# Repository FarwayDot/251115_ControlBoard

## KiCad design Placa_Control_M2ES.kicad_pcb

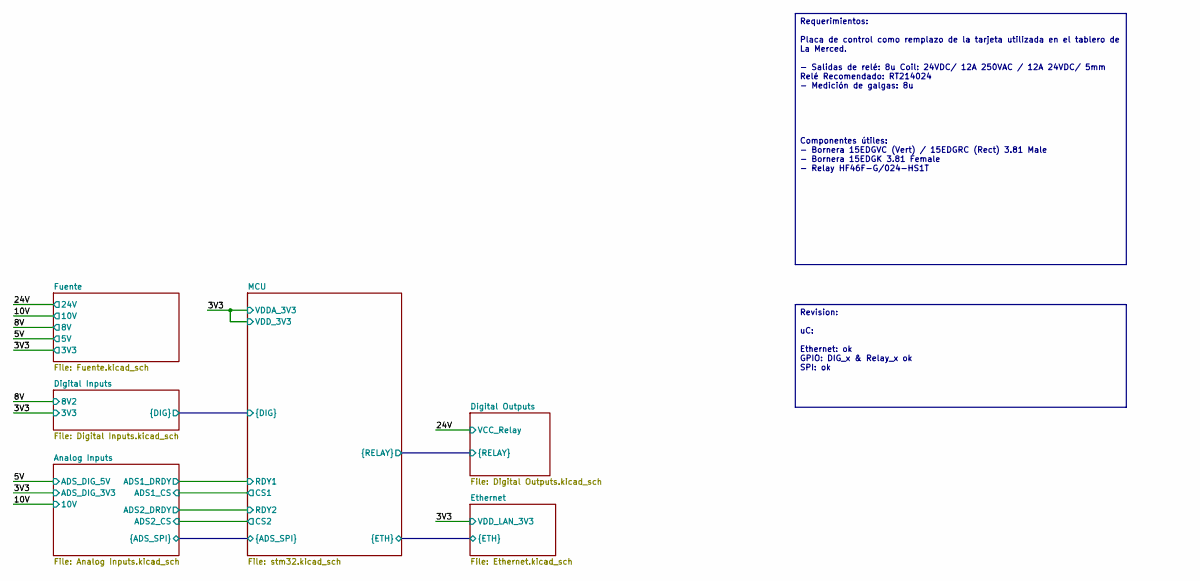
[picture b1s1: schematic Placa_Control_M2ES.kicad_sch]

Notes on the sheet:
Requerimientos: Placa de control como remplazo de la tarjeta utilizada en el tablero de La Merced. - Salidas de relé: 8u Coil: 24VDC/ 12A 250VAC / 12A 24VDC/ 5mm Relé Recomendado: RT214024 - Medición de galgas: 8u Componentes útiles: - Bornera 15EDGVC (Vert) / 15EDGRC (Rect) 3.81 Male - Bornera 15E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
Revision: uC: Ethernet: ok GPIO: DIG_x & Relay_x ok SPI: ok

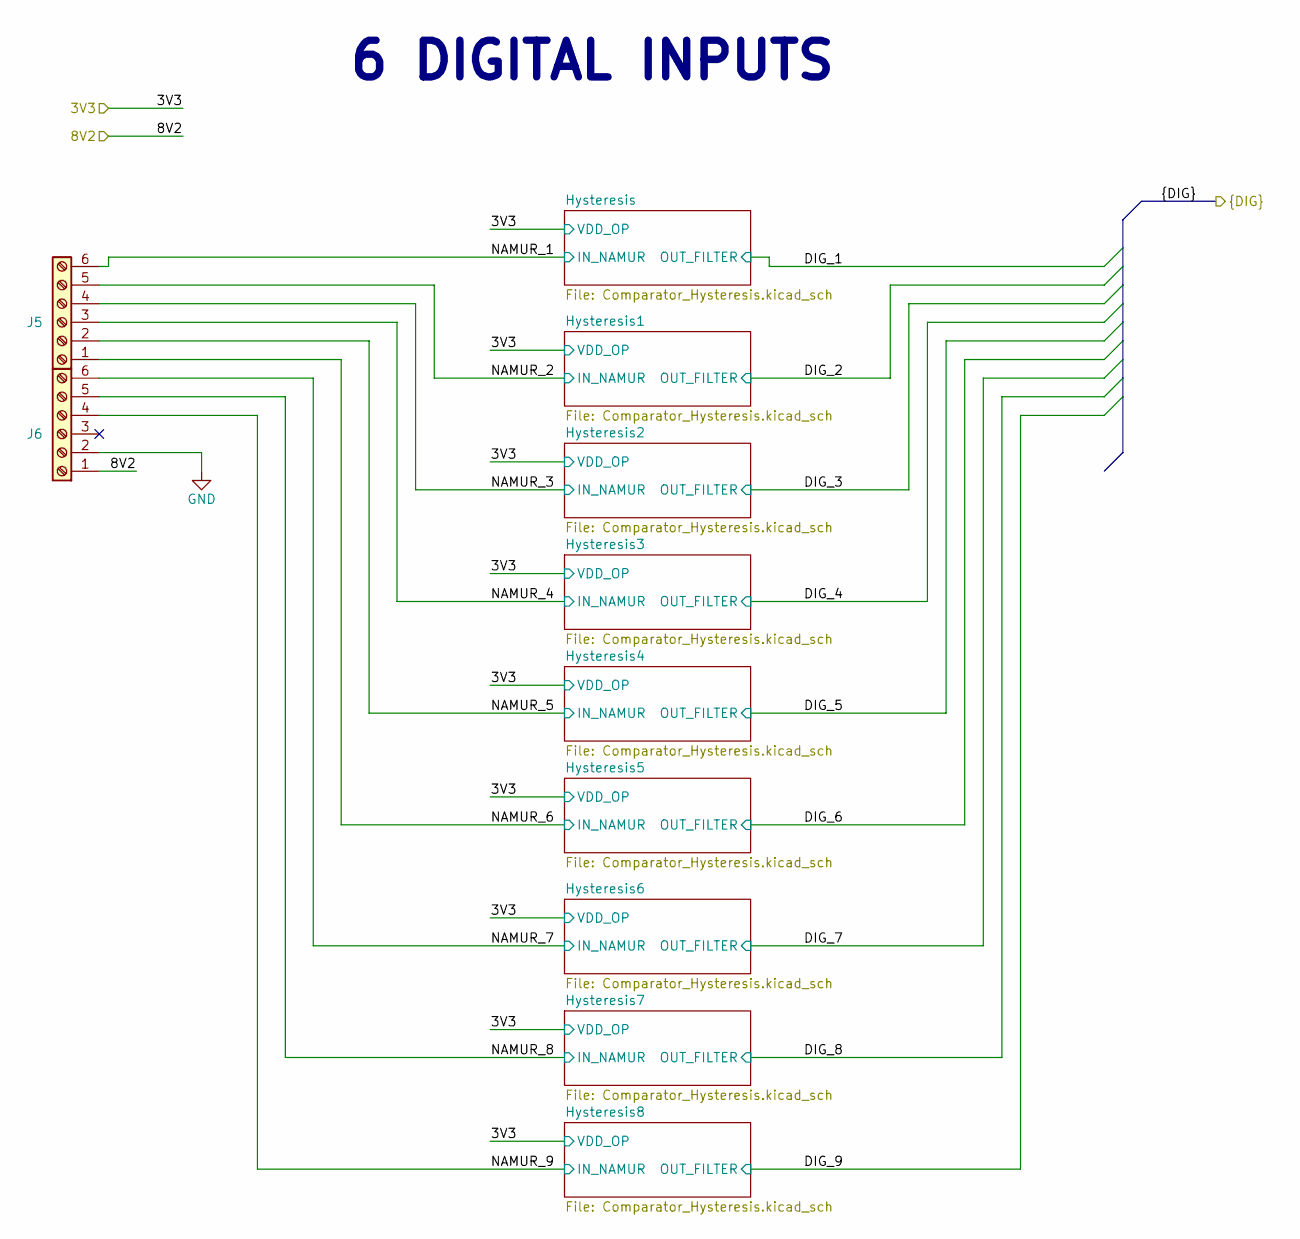
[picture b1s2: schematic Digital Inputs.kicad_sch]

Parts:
J5, J6: Screw_Terminal_01x06; 15EDGVC_6P_3.81mm_Male-Vert_Degson

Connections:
/8V: J6.1; also elsewhere on the board
/Digital Inputs/NAMUR_1: J5.6; also elsewhere on the board
/Digital Inputs/NAMUR_2: J5.5; also elsewhere on the board
/Digital Inputs/NAMUR_3: J5.4; also elsewhere on the board
/Digital Inputs/NAMUR_4: J5.3; also elsewhere on the board
/Digital Inputs/NAMUR_5: J5.2; also elsewhere on the board
/Digital Inputs/NAMUR_6: J5.1; also elsewhere on the board
/Digital Inputs/NAMUR_7: J6.6; also elsewhere on the board
/Digital Inputs/NAMUR_8: J6.5; also elsewhere on the board
/Digital Inputs/NAMUR_9: J6.4; also elsewhere on the board
GND: J6.2; also elsewhere on the board

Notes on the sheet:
6 DIGITAL INPUTS

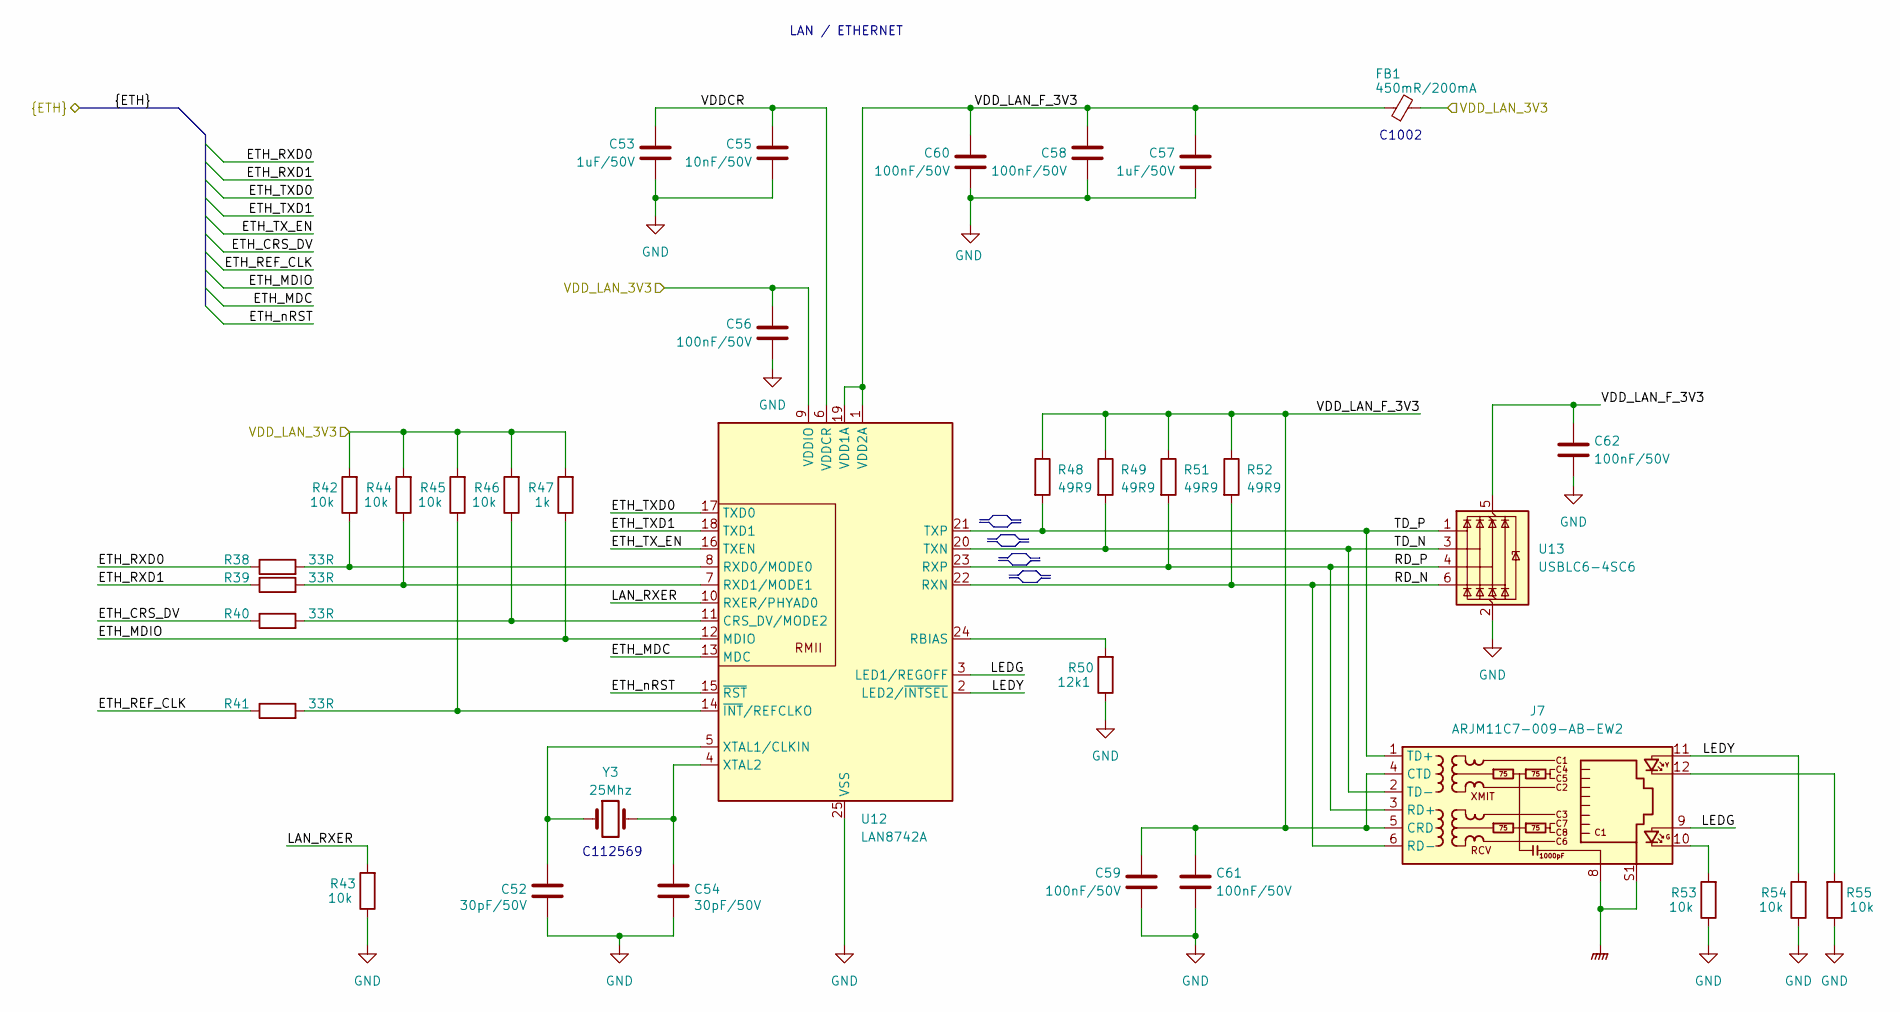
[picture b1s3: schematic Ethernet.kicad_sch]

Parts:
C52, C54: 30pF/50V; C_0603_1608Metric
C53, C57: 1uF/50V; C_0805_2012Metric
C55: 10nF/50V; C_0603_1608Metric
C56, C58, C59, C60, C61, C62: 100nF/50V; C_0603_1608Metric
FB1: 450mR/200mA; L_0603_1608Metric
J7: ARJM11C7-009-AB-EW2; ARJM11C7-009-AB-EW2_Abracon
R38, R39, R40, R41: 33R; R_0603_1608Metric
R42, R43, R44, R45, R46, R53, R54, R55: 10k; R_0603_1608Metric
R47: 1k; R_0603_1608Metric
R48, R49, R51, R52: 49R9; R_0603_1608Metric
R50: 12k1; R_0603_1608Metric
U12: LAN8742A; VQFN-24-1EP_4x4mm_P0.5mm_EP2.5x2.5mm_ThermalVias
U13: USBLC6-4SC6; SOT-23-6
Y3: 25Mhz; Crystal_SMD_5032-2Pin_5.0x3.2mm

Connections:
/Ethernet/ETH_CRS_DV: R40.1; also elsewhere on the board
/Ethernet/ETH_MDC: U12.13 (MDC); also elsewhere on the board
/Ethernet/ETH_MDIO: R47.1, U12.12 (MDIO); also elsewhere on the board
/Ethernet/ETH_REF_CLK: R41.1; also elsewhere on the board
/Ethernet/ETH_RXD0: R38.1; also elsewhere on the board
/Ethernet/ETH_RXD1: R39.1; also elsewhere on the board
/Ethernet/ETH_TXD0: U12.17 (TXD0); also elsewhere on the board
/Ethernet/ETH_TXD1: U12.18 (TXD1); also elsewhere on the board
/Ethernet/ETH_TX_EN: U12.16 (TXEN); also elsewhere on the board
/Ethernet/ETH_nRST: U12.15 (~RST); also elsewhere on the board
/Ethernet/LAN_RXER: R43.2, U12.10 (RXER/PHYAD0)
/Ethernet/LEDG: J7.9, U12.3 (LED1/REGOFF)
/Ethernet/LEDY: J7.11, R54.2, U12.2 (LED2/~INTSEL)
/Ethernet/RD_N: J7.6 (RD-), R52.2, U12.22 (RXN), U13.6 (I/O4)
/Ethernet/RD_P: J7.3 (RD+), R51.2, U12.23 (RXP), U13.4 (I/O3)
/Ethernet/TD_N: J7.2 (TD-), R49.2, U12.20 (TXN), U13.3 (I/O2)
/Ethernet/TD_P: J7.1 (TD+), R48.2, U12.21 (TXP), U13.1 (I/O1)
/Ethernet/VDDCR: C53.1, C55.1, U12.6 (VDDCR)
/Ethernet/VDD_LAN_F_3V3: C57.1, C58.1, C59.1, C60.1, C61.1, C62.1, FB1.1, J7.4 (CTD), J7.5 (CRD), R48.1, R49.1, R51.1, R52.1, U12.1 (VDD2A), U12.19 (VDD1A), U13.5 (VBUS)
GND: C52.2, C53.2, C54.2, C55.2, C56.2, C57.2, C58.2, C59.2, C60.2, C61.2, C62.2, R43.1, R50.1, R53.1, R54.1, R55.1, U12.25 (VSS), U13.2 (GND); also elsewhere on the board
GNDPWR: J7.8, J7.S1, J7.S2
unnamed: J7.10, R53.2
unnamed: J7.12, R55.2
unnamed: R40.2, R46.1, U12.11 (CRS_DV/MODE2)
unnamed: R50.2, U12.24 (RBIAS)
unnamed: R38.2, R42.1, U12.8 (RXD0/MODE0)
unnamed: R39.2, R44.1, U12.7 (RXD1/MODE1)
unnamed: C52.1, U12.5 (XTAL1/CLKIN), Y3.1
unnamed: C54.1, U12.4 (XTAL2), Y3.2
unnamed: R41.2, R45.1, U12.14 (~INT/REFCLKO)

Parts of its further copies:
R14, R17, R19, R21, R23, R24, R25: 10k; R_0603_1608Metric

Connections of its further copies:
/Analog Inputs/IN1_N: R23.2, R25.1; also elsewhere on the board
/Analog Inputs/IN2_N: R17.1; also elsewhere on the board
/Analog Inputs/IN2_P: R14.1; also elsewhere on the board
/Analog Inputs/IN3_N: R19.2, R21.1; also elsewhere on the board
/Analog Inputs/SENS1_A: R24.2; also elsewhere on the board
/Analog Inputs/SENS1_B: R25.2; also elsewhere on the board
/Analog Inputs/SENS2_B: R17.2; also elsewhere on the board
/Analog Inputs/SENS3_B: R21.2; also elsewhere on the board
GND: R14.2, R19.1, R23.1; also elsewhere on the board

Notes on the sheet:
C112569
C1002
LAN / ETHERNET

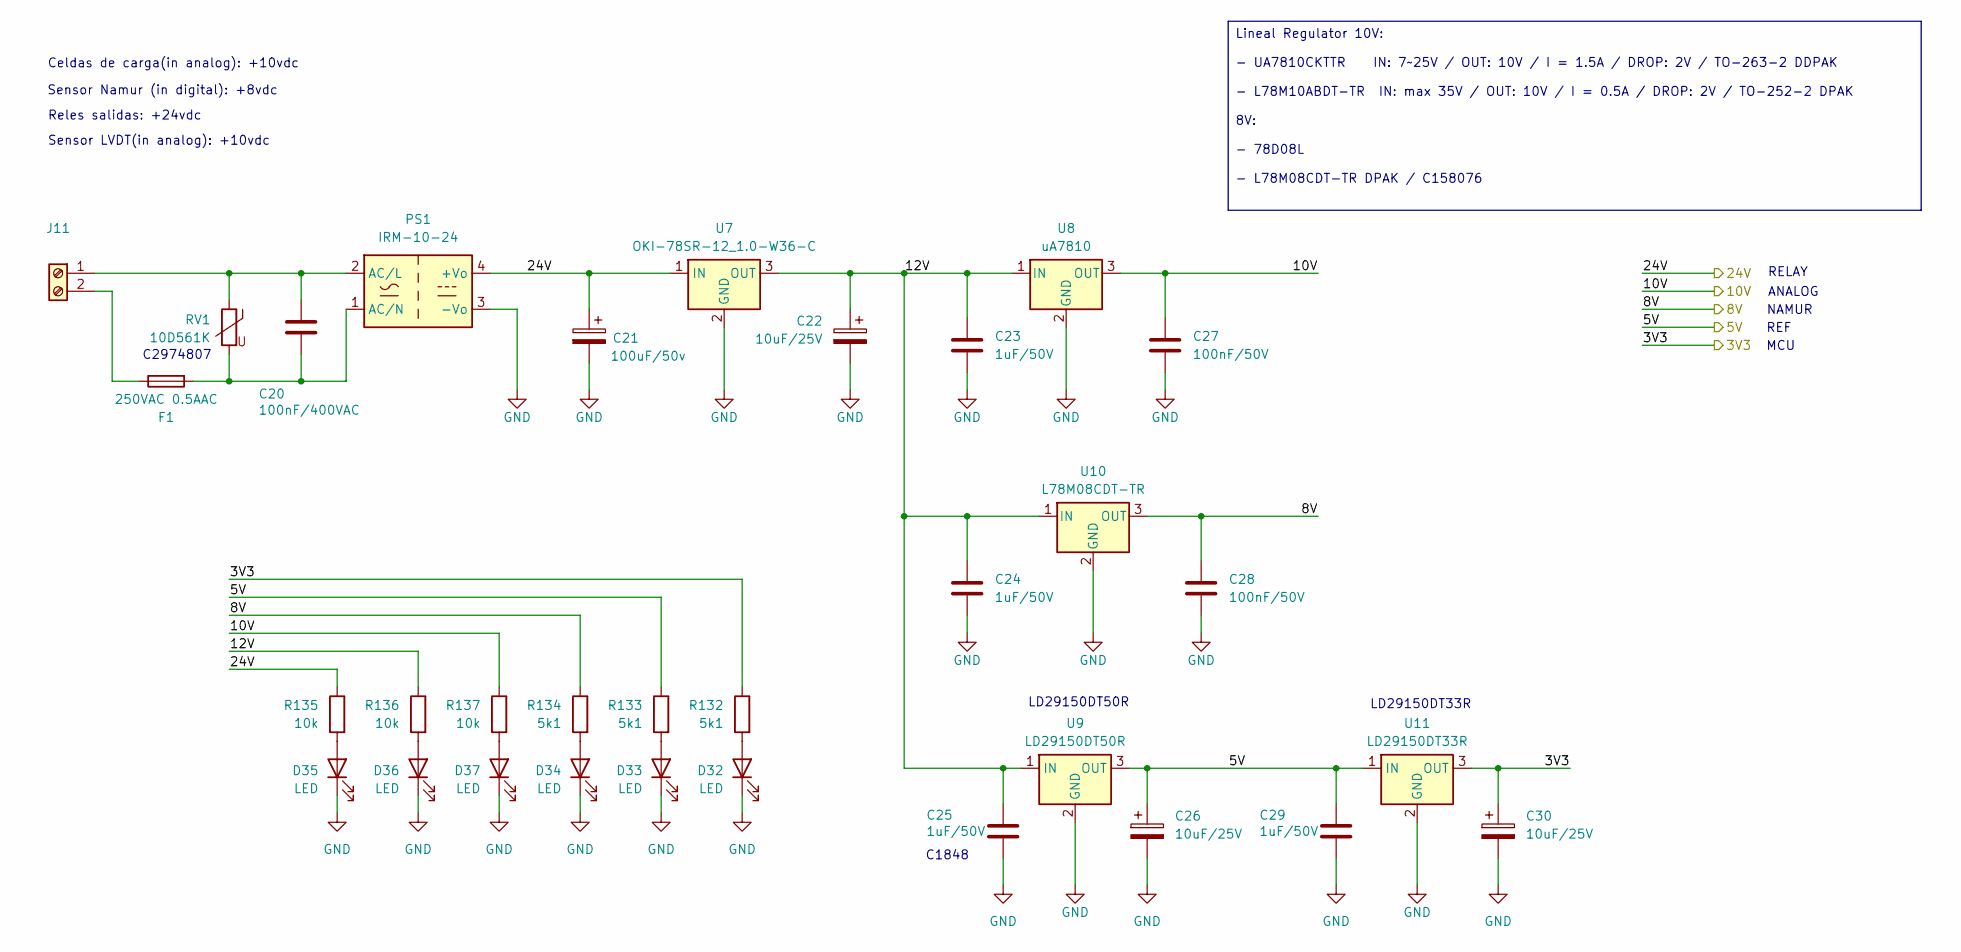
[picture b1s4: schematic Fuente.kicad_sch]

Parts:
C20: 100nF/400VAC; C_Disc_D10.5mm_W5.0mm_P7.50mm
C21: 100uF/50v; CP_Radial_D10.0mm_P5.00mm
C22, C26, C30: 10uF/25V; CP_Radial_D5.0mm_P2.50mm
C23, C24, C25, C29: 1uF/50V; C_1206_3216Metric
C27, C28: 100nF/50V; C_0603_1608Metric
D32, D33, D34, D35, D36, D37: LED; LED_0805_2012Metric
F1: 250VAC 0.5AAC; Fuseholder_TR5_Littelfuse_No560_No460
J11: Screw_Terminal_01x02; DG126_5.0_02P
PS1: IRM-10-24; Converter_ACDC_MeanWell_IRM-10-xx_THT
R132, R133, R134: 5k1; R_0603_1608Metric
R135, R136, R137: 10k; R_0603_1608Metric
RV1: 10D561K; RV_Disc_D12mm_W3.9mm_P7.5mm
U7: OKI-78SR-12_1.0-W36-C; Converter_DCDC_Murata_OKI-78SR_Vertical
U8: uA7810; TO-263-3_TabPin2
U9: LD29150DT50R; TO-252-2
U10: L78M08CDT-TR; TO-252-2
U11: LD29150DT33R; TO-252-2

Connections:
/5V: C26.1, C29.1, R133.1, U9.3 (OUT), U11.1 (IN); also elsewhere on the board
/8V: C28.1, R134.1, U10.3 (OUT); also elsewhere on the board
/10V: C27.1, R137.1, U8.3 (OUT); also elsewhere on the board
/24V: C21.1, PS1.4 (+Vo), R135.1, U7.1 (IN); also elsewhere on the board
/Fuente/12V: C22.1, C23.1, C24.1, C25.1, R136.1, U7.3 (OUT), U8.1 (IN), U9.1 (IN), U10.1 (IN)
GND: C21.2, C22.2, C23.2, C24.2, C25.2, C26.2, C27.2, C28.2, C29.2, C30.2, D32.1 (K), D33.1 (K), D34.1 (K), D35.1 (K), D36.1 (K), D37.1 (K), PS1.3 (-Vo), U7.2 (GND), U8.2 (GND), U9.2 (GND), U10.2 (GND), U11.2 (GND); also elsewhere on the board
unnamed: D32.2 (A), R132.2
unnamed: D33.2 (A), R133.2
unnamed: D34.2 (A), R134.2
unnamed: D35.2 (A), R135.2
unnamed: D36.2 (A), R136.2
unnamed: D37.2 (A), R137.2
unnamed: C20.1, J11.1, PS1.2 (AC/L), RV1.1
unnamed: F1.1, J11.2
unnamed: C20.2, F1.2, PS1.1 (AC/N), RV1.2

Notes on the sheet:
C1848
RELAY
Sensor Namur (in digital): +8vdc
Reles salidas: +24vdc
LD29150DT33R
C2974807
LD29150DT50R
REF
ANALOG
Celdas de carga(in analog): +10vdc
NAMUR
MCU
Sensor LVDT(in analog): +10vdc
Lineal Regulator 10V: - UA7810CKTTR IN: 7~25V / OUT: 10V / I = 1.5A / DROP: 2V / TO-263-2 DDPAK - L78M10ABDT-TR IN: max 35V / OUT: 10V / I = 0.5A / DROP: 2V / TO-252-2 DPAK 8V: - 78D08L - L78M08CDT-TR DPAK / C158076

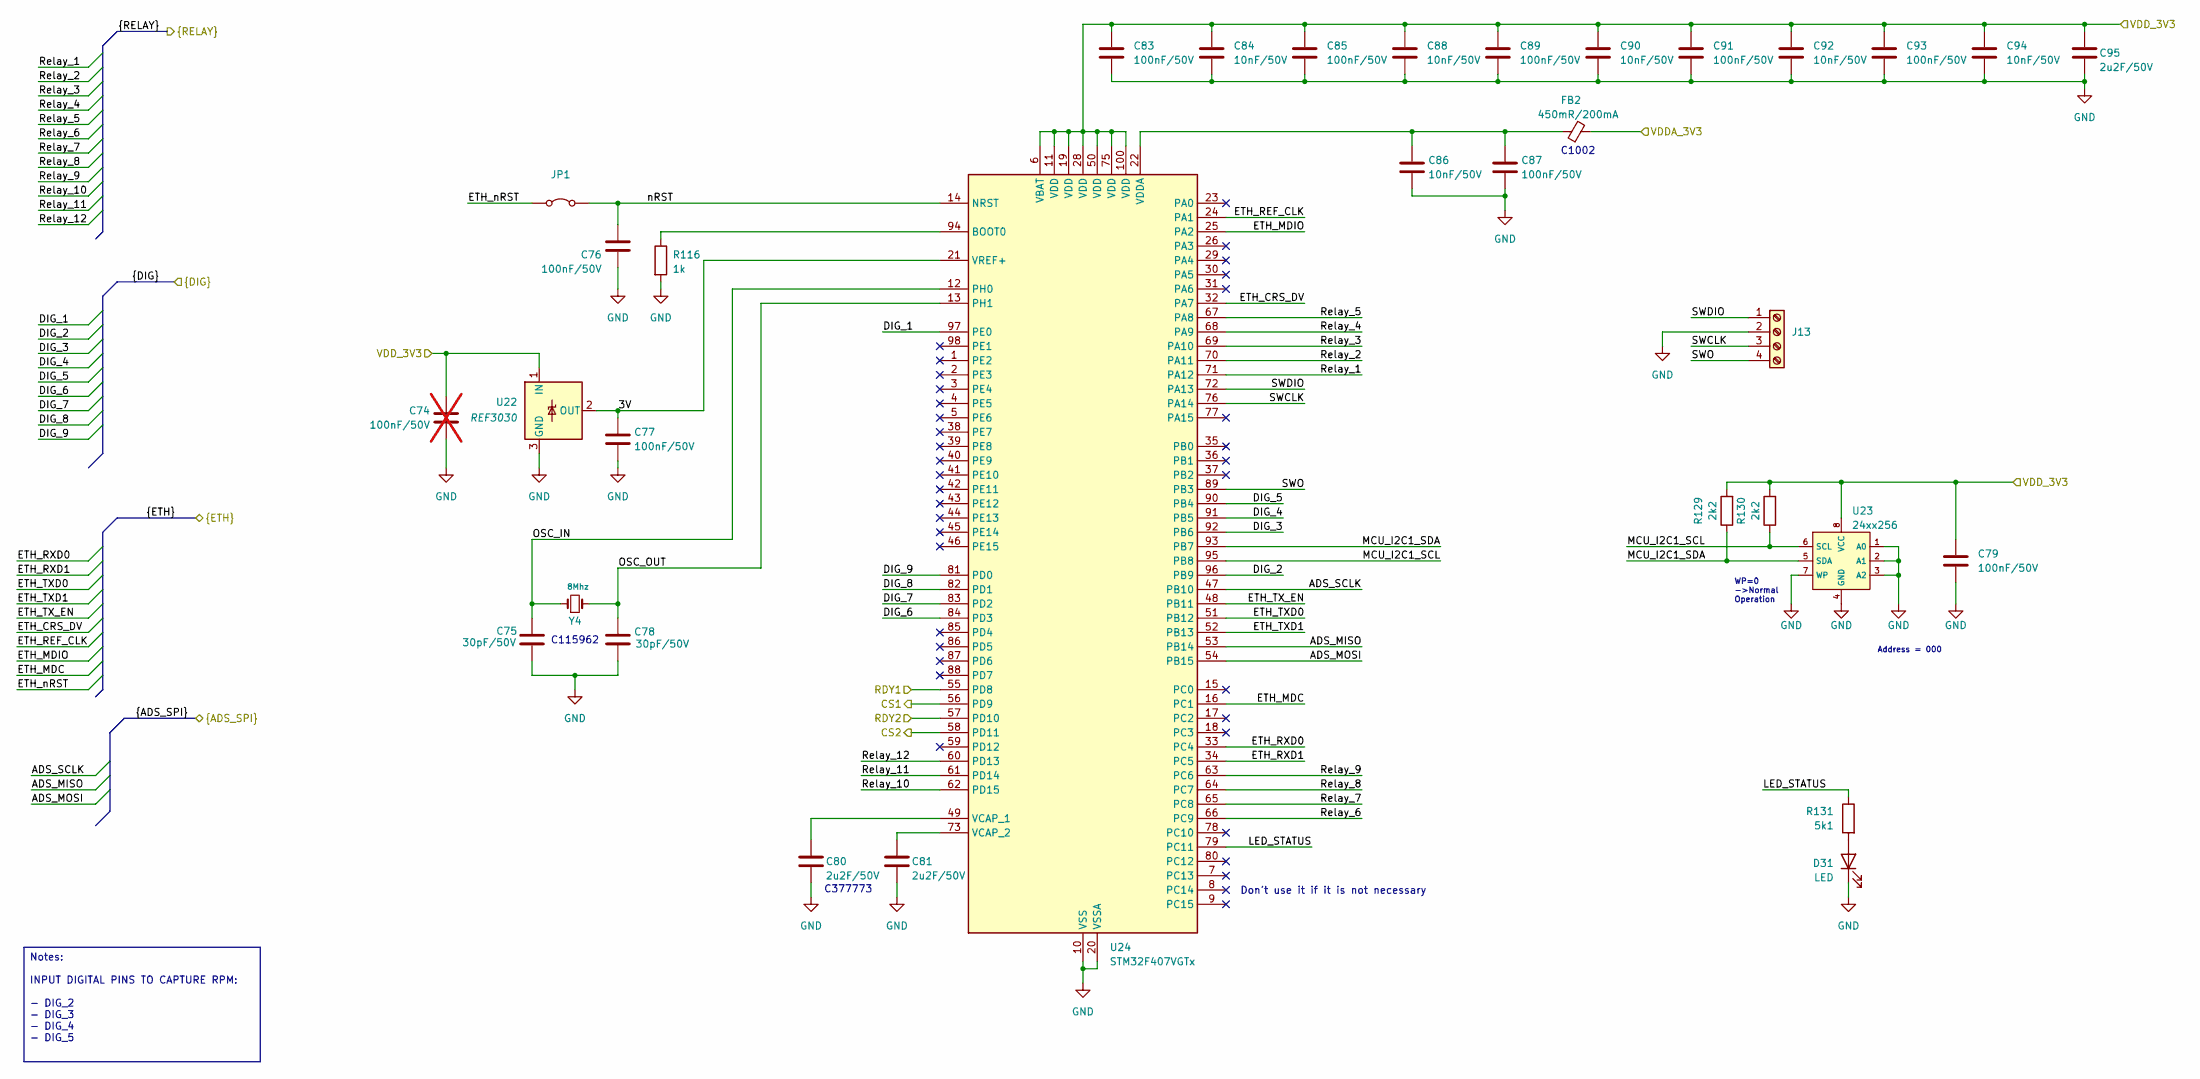
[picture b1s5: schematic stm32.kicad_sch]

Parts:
C74: 100nF/50V; C_0603_1608Metric; not fitted
C75, C78: 30pF/50V; C_0603_1608Metric
C76, C77, C79, C83, C85, C87, C89, C91, C93: 100nF/50V; C_0603_1608Metric
C80, C81, C95: 2u2F/50V; C_0805_2012Metric
C84, C86, C88, C90, C92, C94: 10nF/50V; C_0603_1608Metric
D31: LED; LED_0805_2012Metric
FB2: 450mR/200mA; L_0603_1608Metric
J13: Screw_Terminal_01x04; PinHeader_1x04_P2.54mm_Vertical
JP1: Jumper_2_Bridged; SolderJumper-2_P1.3mm_Open_Pad1.0x1.5mm
R116: 1k; R_0603_1608Metric
R129, R130: 2k2; R_0603_1608Metric
R131: 5k1; R_0603_1608Metric
U22: REF3030; SOT-23
U23: 24xx256; SO-8_3.9x4.9mm_P1.27mm
U24: STM32F407VGTx; LQFP-100_14x14mm_P0.5mm
Y4: 8Mhz; Crystal_SMD_5032-2Pin_5.0x3.2mm

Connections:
/Analog Inputs/ADS1_CS: U24.56 (PD9); also elsewhere on the board
/Analog Inputs/ADS1_DRDY: U24.55 (PD8); also elsewhere on the board
/Analog Inputs/ADS2_CS: U24.58 (PD11); also elsewhere on the board
/Analog Inputs/ADS2_DRDY: U24.57 (PD10); also elsewhere on the board
/Analog Inputs/ADS_MISO: U24.53 (PB14); also elsewhere on the board
/Analog Inputs/ADS_MOSI: U24.54 (PB15); also elsewhere on the board
/Analog Inputs/ADS_SCLK: U24.47 (PB10); also elsewhere on the board
/Digital Inputs/DIG_1: U24.97 (PE0); also elsewhere on the board
/Digital Inputs/DIG_2: U24.96 (PB9); also elsewhere on the board
/Digital Inputs/DIG_3: U24.92 (PB6); also elsewhere on the board
/Digital Inputs/DIG_4: U24.91 (PB5); also elsewhere on the board
/Digital Inputs/DIG_5: U24.90 (PB4); also elsewhere on the board
/Digital Inputs/DIG_6: U24.84 (PD3); also elsewhere on the board
/Digital Inputs/DIG_7: U24.83 (PD2); also elsewhere on the board
/Digital Inputs/DIG_8: U24.82 (PD1); also elsewhere on the board
/Digital Inputs/DIG_9: U24.81 (PD0); also elsewhere on the board
/Digital Outputs/Relay_1: U24.71 (PA12); also elsewhere on the board
/Digital Outputs/Relay_2: U24.70 (PA11); also elsewhere on the board
/Digital Outputs/Relay_3: U24.69 (PA10); also elsewhere on the board
/Digital Outputs/Relay_4: U24.68 (PA9); also elsewhere on the board
/Digital Outputs/Relay_5: U24.67 (PA8); also elsewhere on the board
/Digital Outputs/Relay_6: U24.66 (PC9); also elsewhere on the board
/Digital Outputs/Relay_7: U24.65 (PC8); also elsewhere on the board
/Digital Outputs/Relay_8: U24.64 (PC7); also elsewhere on the board
/Digital Outputs/Relay_9: U24.63 (PC6); also elsewhere on the board
/Digital Outputs/Relay_10: U24.62 (PD15); also elsewhere on the board
/Digital Outputs/Relay_11: U24.61 (PD14); also elsewhere on the board
/Digital Outputs/Relay_12: U24.60 (PD13); also elsewhere on the board
/Ethernet/ETH_CRS_DV: U24.32 (PA7); also elsewhere on the board
/Ethernet/ETH_MDC: U24.16 (PC1); also elsewhere on the board
/Ethernet/ETH_MDIO: U24.25 (PA2); also elsewhere on the board
/Ethernet/ETH_REF_CLK: U24.24 (PA1); also elsewhere on the board
/Ethernet/ETH_RXD0: U24.33 (PC4); also elsewhere on the board
/Ethernet/ETH_RXD1: U24.34 (PC5); also elsewhere on the board
/Ethernet/ETH_TXD0: U24.51 (PB12); also elsewhere on the board
/Ethernet/ETH_TXD1: U24.52 (PB13); also elsewhere on the board
/Ethernet/ETH_TX_EN: U24.48 (PB11); also elsewhere on the board
/Ethernet/ETH_nRST: JP1.1 (A); also elsewhere on the board
/MCU/3V: C77.1, U22.2 (OUT), U24.21 (VREF+)
/MCU/LED_STATUS: R131.1, U24.79 (PC11)
/MCU/MCU_I2C1_SCL: R130.1, U23.6 (SCL), U24.95 (PB8)
/MCU/MCU_I2C1_SDA: R129.1, U23.5 (SDA), U24.93 (PB7)
/MCU/OSC_IN: C75.1, U24.12 (PH0), Y4.1
/MCU/OSC_OUT: C78.1, U24.13 (PH1), Y4.2
/MCU/SWCLK: J13.3, U24.76 (PA14)
/MCU/SWDIO: J13.1, U24.72 (PA13)
/MCU/SWO: J13.4, U24.89 (PB3)
/MCU/nRST: C76.1, JP1.2 (B), U24.14 (NRST)
GND: C75.2, C76.2, C77.2, C78.2, C79.2, C80.2, C81.2, C83.2, C84.2, C85.2, C86.2, C87.2, C88.2, C89.2, C90.2, C91.2, C92.2, C93.2, C94.2, C95.2, D31.1 (K), J13.2, R116.2, U22.3 (GND), U23.1 (A0), U23.2 (A1), U23.3 (A2), U23.4 (GND), U23.7 (WP), U24.10 (VSS), U24.20 (VSSA), U24.27 (VSS), U24.74 (VSS), U24.99 (VSS); also elsewhere on the board
unnamed: D31.2 (A), R131.2
unnamed: R116.1, U24.94 (BOOT0)
unnamed: C80.1, U24.49 (VCAP_1)
unnamed: C81.1, U24.73 (VCAP_2)
unnamed: C86.1, C87.1, FB2.1, U24.22 (VDDA)

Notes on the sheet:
C115962
Address = 000
C377773
C1002
WP=0 ->Normal Operation
Don't use it if it is not necessary
Notes: INPUT DIGITAL PINS TO CAPTURE RPM: - DIG_2 - DIG_3 - DIG_4 - DIG_5

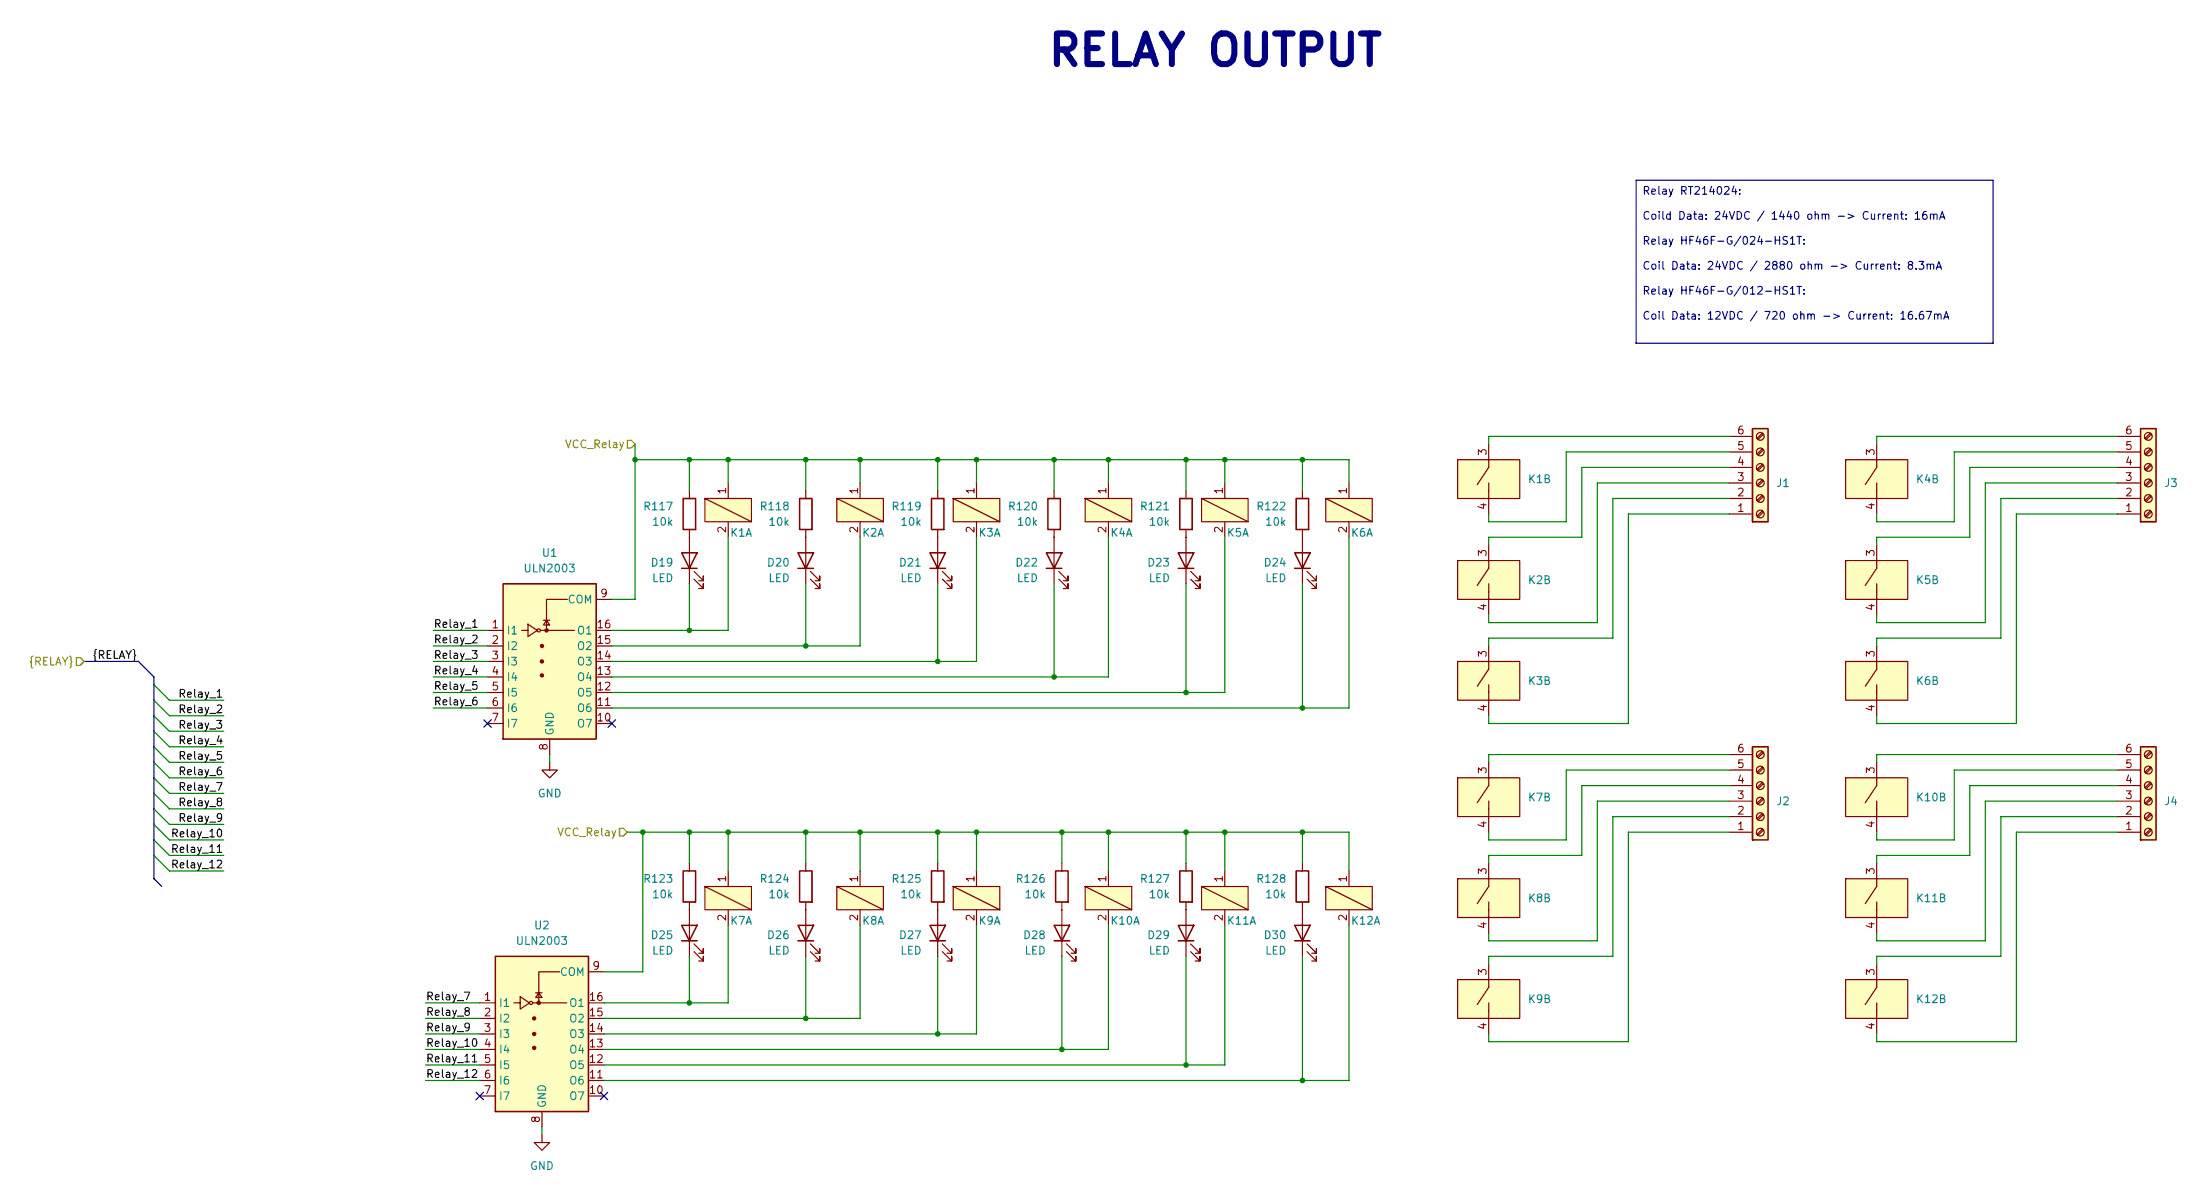
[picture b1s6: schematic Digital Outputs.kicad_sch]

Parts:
D19, D20, D21, D22, D23, D24, D25, D26, D27, D28, D29, D30: LED; LED_0805_2012Metric
J1, J2, J3, J4: Screw_Terminal_01x06; 15EDGVC_6P_3.81mm_Male-Vert_Degson
K1, K2, K3, K4, K5, K6, K7, K8, K9, K10, K11, K12: HF46F-G; Relay_HF46F-G_Hongfa
R117, R118, R119, R120, R121, R122, R123, R124, R125, R126, R127, R128: 10k; R_0603_1608Metric
U1, U2: ULN2003; SOIC-16_3.9x9.9mm_P1.27mm

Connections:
/24V: K1.1, K2.1, K3.1, K4.1, K5.1, K6.1, K7.1, K8.1, K9.1, K10.1, K11.1, K12.1, R117.1, R118.1, R119.1, R120.1, R121.1, R122.1, R123.1, R124.1, R125.1, R126.1, R127.1, R128.1, U1.9 (COM), U2.9 (COM); also elsewhere on the board
/Digital Outputs/Relay_1: U1.1 (I1); also elsewhere on the board
/Digital Outputs/Relay_2: U1.2 (I2); also elsewhere on the board
/Digital Outputs/Relay_3: U1.3 (I3); also elsewhere on the board
/Digital Outputs/Relay_4: U1.4 (I4); also elsewhere on the board
/Digital Outputs/Relay_5: U1.5 (I5); also elsewhere on the board
/Digital Outputs/Relay_6: U1.6 (I6); also elsewhere on the board
/Digital Outputs/Relay_7: U2.1 (I1); also elsewhere on the board
/Digital Outputs/Relay_8: U2.2 (I2); also elsewhere on the board
/Digital Outputs/Relay_9: U2.3 (I3); also elsewhere on the board
/Digital Outputs/Relay_10: U2.4 (I4); also elsewhere on the board
/Digital Outputs/Relay_11: U2.5 (I5); also elsewhere on the board
/Digital Outputs/Relay_12: U2.6 (I6); also elsewhere on the board
GND: U1.8 (GND), U2.8 (GND); also elsewhere on the board
unnamed: D19.2 (A), R117.2
unnamed: D19.1 (K), K1.2, U1.16 (O1)
unnamed: D20.2 (A), R118.2
unnamed: D20.1 (K), K2.2, U1.15 (O2)
unnamed: D21.2 (A), R119.2
unnamed: D21.1 (K), K3.2, U1.14 (O3)
unnamed: D22.2 (A), R120.2
unnamed: D22.1 (K), K4.2, U1.13 (O4)
unnamed: D23.2 (A), R121.2
unnamed: D23.1 (K), K5.2, U1.12 (O5)
unnamed: D24.2 (A), R122.2
unnamed: D24.1 (K), K6.2, U1.11 (O6)
unnamed: D25.2 (A), R123.2
unnamed: D25.1 (K), K7.2, U2.16 (O1)
unnamed: D26.2 (A), R124.2
unnamed: D26.1 (K), K8.2, U2.15 (O2)
unnamed: D27.2 (A), R125.2
unnamed: D27.1 (K), K9.2, U2.14 (O3)
unnamed: D28.2 (A), R126.2
unnamed: D28.1 (K), K10.2, U2.13 (O4)
unnamed: D29.2 (A), R127.2
unnamed: D29.1 (K), K11.2, U2.12 (O5)
unnamed: D30.2 (A), R128.2
unnamed: D30.1 (K), K12.2, U2.11 (O6)
unnamed: J1.1, K3.4 (NO)
unnamed: J1.2, K3.3 (COM)
unnamed: J1.3, K2.4 (NO)
unnamed: J1.4, K2.3 (COM)
unnamed: J1.5, K1.4 (NO)
unnamed: J1.6, K1.3 (COM)
unnamed: J2.1, K9.4 (NO)
unnamed: J2.2, K9.3 (COM)
unnamed: J2.3, K8.4 (NO)
unnamed: J2.4, K8.3 (COM)
unnamed: J2.5, K7.4 (NO)
unnamed: J2.6, K7.3 (COM)
unnamed: J3.1, K6.4 (NO)
unnamed: J3.2, K6.3 (COM)
unnamed: J3.3, K5.4 (NO)
unnamed: J3.4, K5.3 (COM)
unnamed: J3.5, K4.4 (NO)
unnamed: J3.6, K4.3 (COM)
unnamed: J4.1, K12.4 (NO)
unnamed: J4.2, K12.3 (COM)
unnamed: J4.3, K11.4 (NO)
unnamed: J4.4, K11.3 (COM)
unnamed: J4.5, K10.4 (NO)
unnamed: J4.6, K10.3 (COM)

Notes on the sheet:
RELAY OUTPUT
Relay RT214024: Coild Data: 24VDC / 1440 ohm -> Current: 16mA Relay HF46F-G/024-HS1T: Coil Data: 24VDC / 2880 ohm -> Current: 8.3mA Relay HF46F-G/012-HS1T: Coil Data: 12VDC / 720 ohm -> Current: 16.67mA
